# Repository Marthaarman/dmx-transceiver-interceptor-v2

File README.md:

# INTERCEPTOR PCB V2

Newest version of:
https://github.com/Marthaarman/dmx_interceptor_PCB

Works with:
https://github.com/Marthaarman/dmx-transceiver-esp

Based on:
https://www.mathertel.de/Arduino/DMXShield

BOM:
(soon)

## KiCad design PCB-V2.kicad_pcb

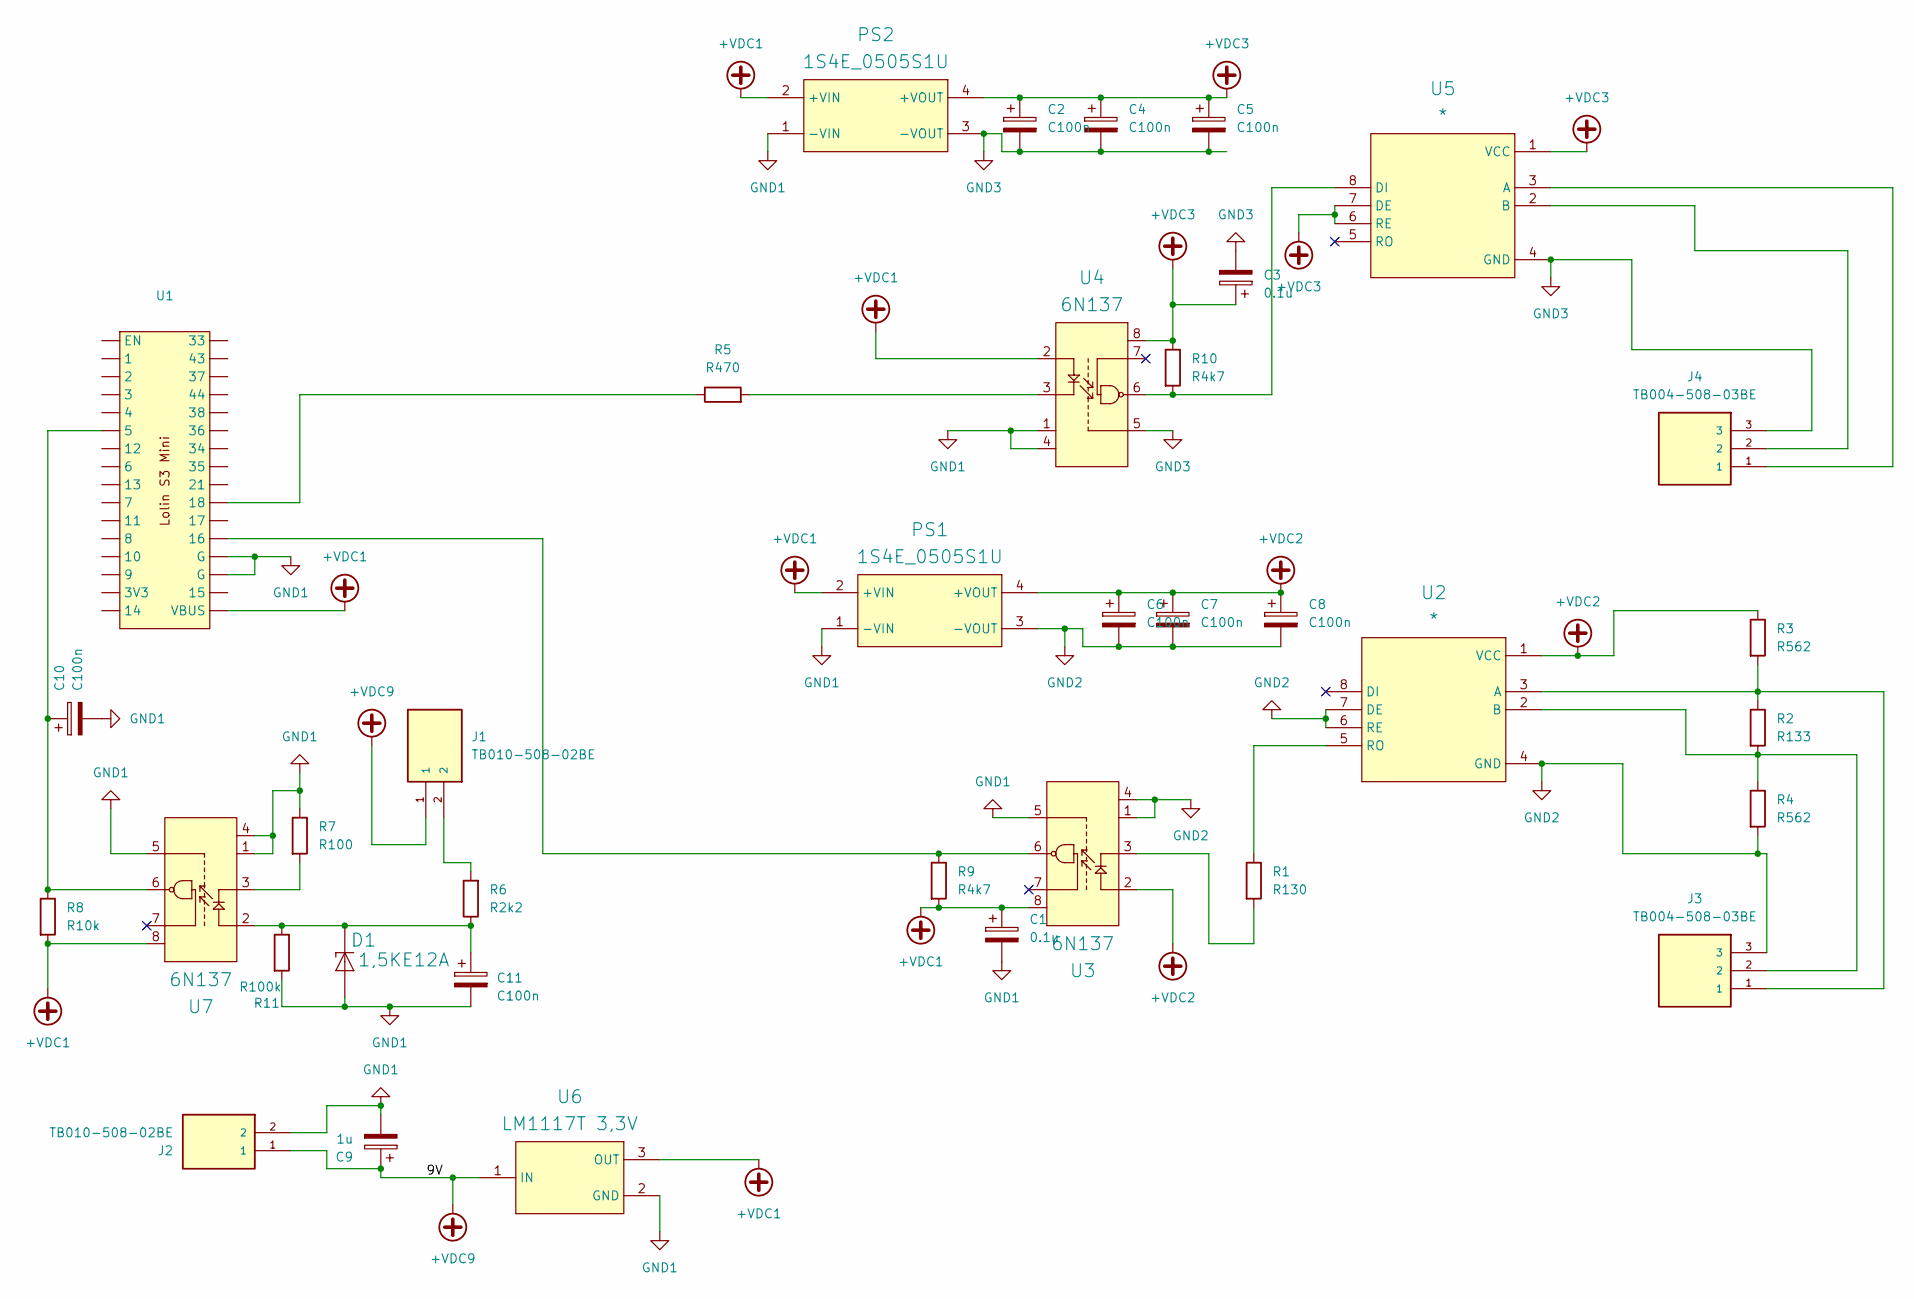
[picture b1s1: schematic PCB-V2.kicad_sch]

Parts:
C1, C3: 0.1u; CP_Radial_D5.0mm_P2.50mm
C2, C4, C5, C6, C7, C8, C10, C11: C100n; CP_Radial_D5.0mm_P2.50mm
C9: 1u; CP_Radial_D5.0mm_P2.50mm
D1: 1,5KE12A; DIOAD1586W101L900D530; Digi-Key_Part_Number 1.5KE12ALFTR-ND
J1, J2: TB010-508-02BE; CUI_TB010-508-02BE
J3, J4: TB004-508-03BE; CUI_TB004-508-03BE
PS1, PS2: 1S4E_0505S1U; CONV_1S4E_0505S1U
R1: R130; R_THT
R2: R133; R_THT
R3, R4: R562; R_THT
R5: R470; R_THT
R6: R2k2; R_THT
R7: R100; R_THT
R8: R10k; R_THT
R9, R10: R4k7; R_THT
R11: R100k; R_THT
U1: WEMOS_lolin_s3_mini
U2, U5: *; max485_to_rs485
U3, U4, U7: 6N137; DIP762W50P254L1016H465Q8
U6: LM1117T 3,3V; TO254P482X997X1880-3P

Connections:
+VDC1: C1.1, PS1.2 (+VIN), PS2.2 (+VIN), R8.2, R9.2, U1.VBUS, U3.8 (VCC), U4.2 (A), U6.3 (OUT), U7.8 (VCC)
+VDC2: C6.1, C7.1, C8.1, PS1.4 (+VOUT), R3.1, U2.1 (VCC), U3.2 (A)
+VDC3: C2.1, C3.1, C4.1, C5.1, PS2.4 (+VOUT), R10.1, U4.8 (VCC), U5.1 (VCC), U5.6 (RE), U5.7 (DE)
+VDC9: C9.1, J1.1, J2.1, U6.1 (IN)
GND1: C1.2, C9.2, C10.2, C11.2, D1.A, J2.2, PS1.1 (-VIN), PS2.1 (-VIN), R7.1, R11.2, U1.GND (G), U3.5 (GND), U4.1 (NC), U4.4 (NC), U6.2 (GND), U7.1 (NC), U7.4 (NC), U7.5 (GND)
GND2: C6.2, C7.2, C8.2, J3.3, PS1.3 (-VOUT), R4.2, U2.4 (GND), U2.6 (RE), U2.7 (DE), U3.1 (NC), U3.4 (NC)
GND3: C2.2, C3.2, C4.2, C5.2, J4.3, PS2.3 (-VOUT), U4.5 (GND), U5.4 (GND)
unnamed: J1.2, R6.2
unnamed: R5.1, U1.18
unnamed: J3.1, R2.1, R3.2, U2.3 (A)
unnamed: J3.2, R2.2, R4.1, U2.2 (B)
unnamed: R1.1, U2.5 (RO)
unnamed: R1.2, U3.3 (C)
unnamed: R9.1, U1.16, U3.6 (VO)
unnamed: R5.2, U4.3 (C)
unnamed: R10.2, U4.6 (VO), U5.8 (DI)
unnamed: J4.1, U5.3 (A)
unnamed: J4.2, U5.2 (B)
unnamed: C11.1, D1.C, R6.1, R11.1, U7.2 (A)
unnamed: R7.2, U7.3 (C)
unnamed: C10.1, R8.1, U1.5, U7.6 (VO)

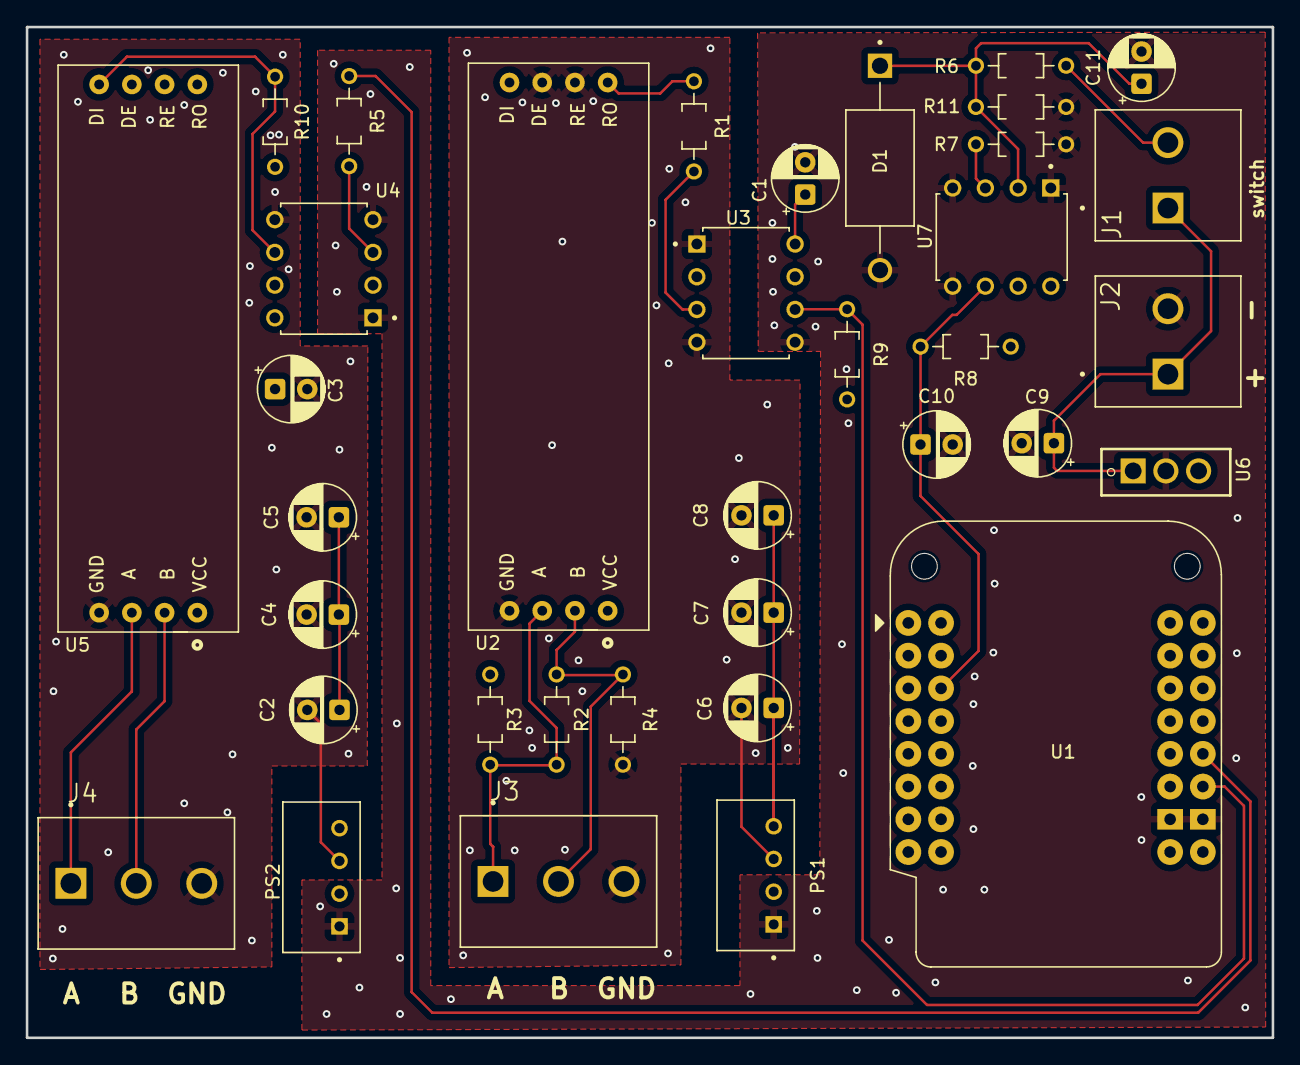
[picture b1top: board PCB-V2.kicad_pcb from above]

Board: 4 copper layers, 96.7 x 78.4 mm, 36 parts (0 on the bottom side), 21 nets.

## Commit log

2025-10-10 init
2025-10-10 adding schematic
2026-02-09 upgrade to more robust switch network
2026-05-01 more robustness in switch pin
